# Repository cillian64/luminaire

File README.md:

# Luminaire

A small light intended to hang in my tent for camping.  Powered by a single AA
battery (lifetime should be 10-20 hours depending on battery capacity and
brightness setting).  Uses the handy ZXSC310 from Diodes Inc as a step-up
(boost) converter.

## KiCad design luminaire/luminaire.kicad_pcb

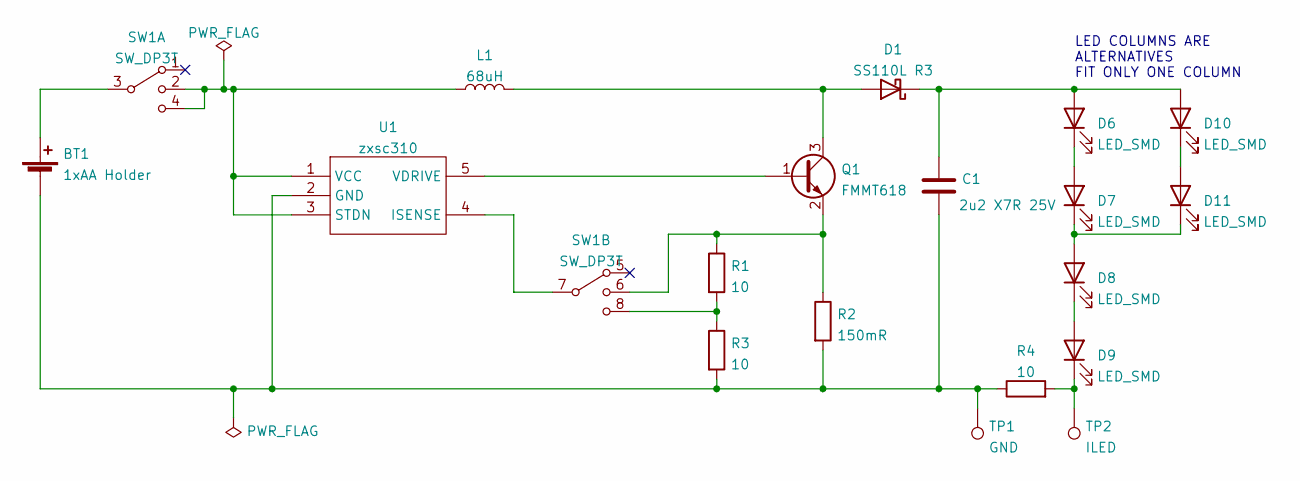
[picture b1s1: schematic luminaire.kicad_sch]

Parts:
BT1: 1xAA Holder; BatteryHolder_Keystone_2460_1xAA; Farnell 3126558
C1: 2u2 X7R 25V; C_0805_2012Metric_Pad1.18x1.45mm_HandSolder; Farnell 1657931
D1: SS110L R3; D_SMA; Farnell 1559156
D6, D7, D8, D9, D10, D11: LED_SMD; LED_Cree-XQ_HandSoldering; Farnell 1855550
L1: 68uH; L_TDK_SLF6045; Farnell 2917136
Q1: FMMT618; SOT-23; Farnell 9526439
R1, R3, R4: 10; R_0805_2012Metric_Pad1.20x1.40mm_HandSolder; Farnell 2331768
R2: 150mR; R_0805_2012Metric_Pad1.20x1.40mm_HandSolder; Farnell 3790820
SW1: SW_DP3T; CL-SB-23B-0XX; Farnell 2978768
TP1: GND; TestPoint_Pad_D2.0mm
TP2: ILED; TestPoint_Pad_D2.0mm
U1: zxsc310; SOT-23-5_HandSoldering; Farnell 3483179

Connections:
unnamed: BT1.1 (+), SW1.3
unnamed: BT1.2 (-), C1.2, R2.2, R3.2, R4.1, TP1.1, U1.2 (GND)
unnamed: C1.1, D1.1 (K), D6.2 (A), D10.2 (A)
unnamed: D1.2 (A), L1.2, Q1.3 (C)
unnamed: D6.1 (K), D7.2 (A)
unnamed: D8.1 (K), D9.2 (A)
unnamed: D9.1 (K), R4.2, TP2.1
unnamed: D10.1 (K), D11.2 (A)
unnamed: D7.1 (K), D8.2 (A), D11.1 (K)
unnamed: L1.1, SW1.2, SW1.4, U1.1 (VCC), U1.3 (STDN)
unnamed: Q1.1 (B), U1.5 (VDRIVE)
unnamed: Q1.2 (E), R1.1, R2.1, SW1.6
unnamed: R1.2, R3.1, SW1.8
unnamed: SW1.7, U1.4 (ISENSE)

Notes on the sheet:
LED COLUMNS ARE ALTERNATIVES FIT ONLY ONE COLUMN

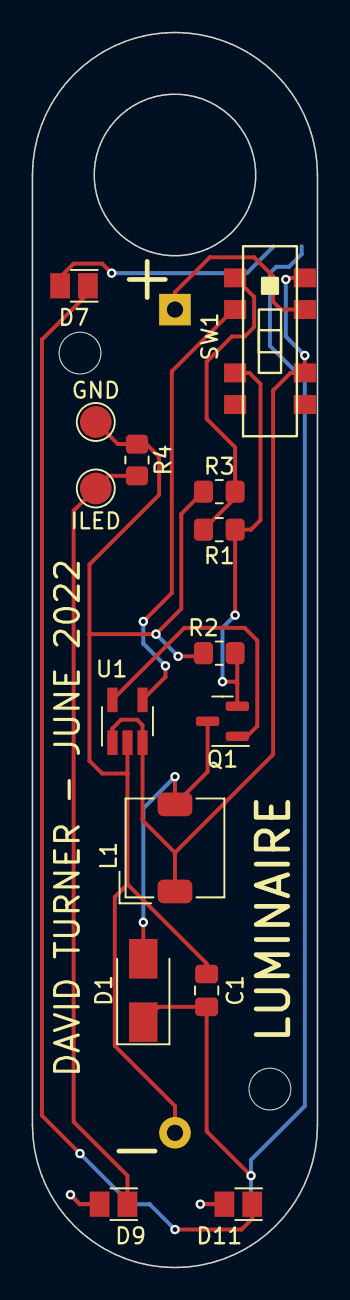
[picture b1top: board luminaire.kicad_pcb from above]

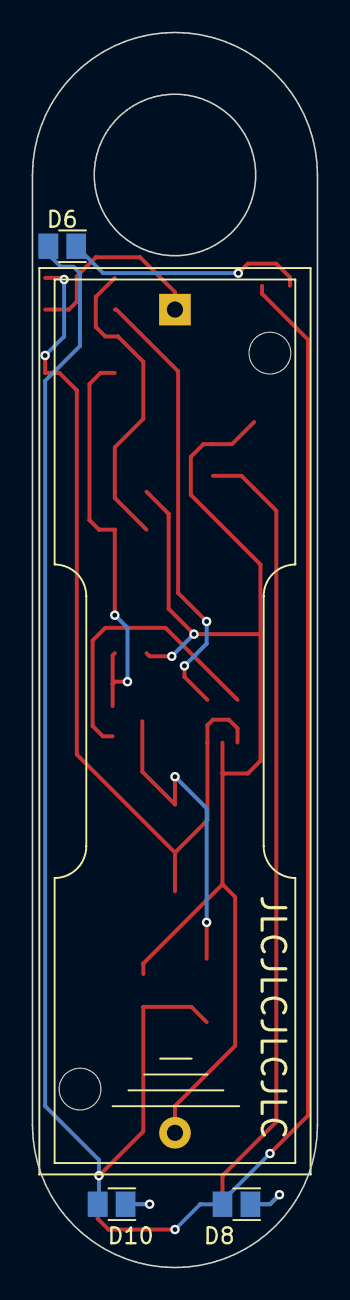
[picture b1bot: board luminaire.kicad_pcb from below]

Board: 2 copper layers, 18.0 x 78.0 mm, 19 parts (4 on the bottom side), 14 nets.

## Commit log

2022-06-17 First draft with PTH LEDs
    Schematic, PCB placement with PTH LEDs (no routing)
2022-06-17 Remove PTH LEDs
    They are kinda massive, make layout awkward, and have really narrow
    viewing angles.
2022-06-17 Finalise design
2022-06-17 Finalise BOM and gerbers
2022-06-17 Trim pins on battery holder 3d model
2022-06-17 Add render, license, and readme
2022-07-15 Annotate schematic with measured currents
